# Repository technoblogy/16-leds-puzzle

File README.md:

# 16 LEDs Puzzle
A puzzle based on an ATtiny404 (or ATtiny204) in which you have to press the right buttons to light up all the LEDs.

See <http://www.technoblogy.com/show?3PO0>.

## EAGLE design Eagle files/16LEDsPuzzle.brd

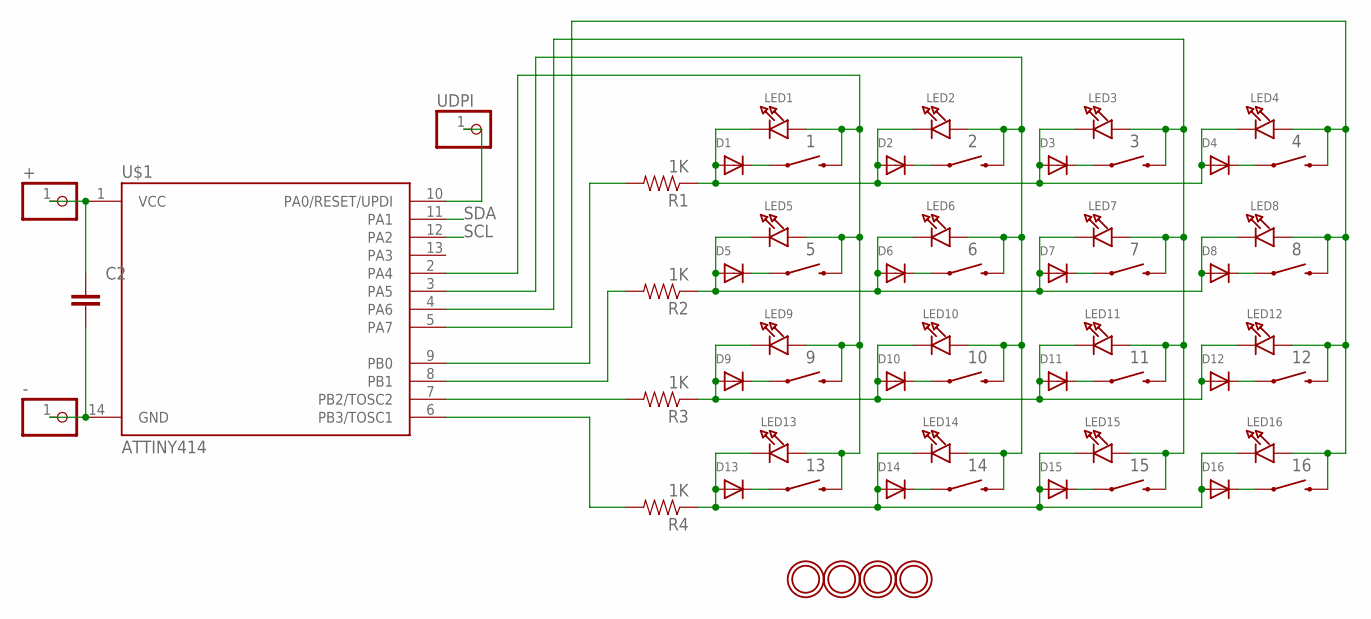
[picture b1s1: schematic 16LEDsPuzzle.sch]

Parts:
1, 2, 3, 4, 5, 6, 7, 8, 9, 10, 11, 12, 13, 14, 15, 16: SWITCH-MOMENTARY-2SMD-4; TACTILE_SWITCH_TALL
+: HEADER-1X1ROUND; 1X01_ROUND
-: HEADER-1X1ROUND; 1X01_ROUND
C2: 100n; 0805
D1, D2, D3, D4, D5, D6, D7, D8, D9, D10, D11, D12, D13, D14, D15, D16: DIODESOD-123; SOD-123
LED1, LED2, LED3, LED4, LED5, LED6, LED7, LED8, LED9, LED10, LED11, LED12, LED13, LED14, LED15, LED16: GREEN; CHIPLED_0805_NOOUTLINE
R1, R2, R3, R4: 1K; 0805
U$1: ATTINY414; SO14
U$2, U$3, U$4, U$5: MOUNTINGHOLE2.5; MOUNTINGHOLE_2.5_PLATED
UDPI: HEADER-1X1ROUND; 1X01_ROUND

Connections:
GND: -.1, C2.2, U$1.14 (GND)
unnamed: R1.2, U$1.9 (PB0)
unnamed: 1.B2 (2), 5.B2 (2), 9.B2 (2), 13.B2 (2), LED1.A, LED5.A, LED9.A, LED13.A, U$1.2 (PA4)
unnamed: 1.A2 (1), D1.C
unnamed: D1.A, D2.A, D3.A, D4.A, LED1.C, LED2.C, LED3.C, LED4.C, R1.1
unnamed: 5.A2 (1), D5.C
unnamed: 2.A2 (1), D2.C
unnamed: 2.B2 (2), 6.B2 (2), 10.B2 (2), 14.B2 (2), LED2.A, LED6.A, LED10.A, LED14.A, U$1.3 (PA5)
unnamed: D5.A, D6.A, D7.A, D8.A, LED5.C, LED6.C, LED7.C, LED8.C, R2.1
unnamed: 6.A2 (1), D6.C
unnamed: 3.A2 (1), D3.C
unnamed: R2.2, U$1.8 (PB1)
unnamed: 3.B2 (2), 7.B2 (2), 11.B2 (2), 15.B2 (2), LED3.A, LED7.A, LED11.A, LED15.A, U$1.4 (PA6)
unnamed: R3.2, U$1.7 (PB2/TOSC2)
unnamed: 4.A2 (1), D4.C
unnamed: 4.B2 (2), 8.B2 (2), 12.B2 (2), 16.B2 (2), LED4.A, LED8.A, LED12.A, LED16.A, U$1.5 (PA7)
unnamed: 7.A2 (1), D7.C
unnamed: R4.2, U$1.6 (PB3/TOSC1)
unnamed: 8.A2 (1), D8.C
unnamed: 9.A2 (1), D9.C
unnamed: D9.A, D10.A, D11.A, D12.A, LED9.C, LED10.C, LED11.C, LED12.C, R3.1
unnamed: 10.A2 (1), D10.C
unnamed: 11.A2 (1), D11.C
unnamed: U$1.10 (PA0/RESET/UPDI), UDPI.1
unnamed: 12.A2 (1), D12.C
unnamed: 13.A2 (1), D13.C
unnamed: D13.A, D14.A, D15.A, D16.A, LED13.C, LED14.C, LED15.C, LED16.C, R4.1
unnamed: 14.A2 (1), D14.C
unnamed: 15.A2 (1), D15.C
unnamed: 16.A2 (1), D16.C
SCL: U$1.12 (PA2)
SDA: U$1.11 (PA1)
VCC: +.1, C2.1, U$1.1 (VCC)

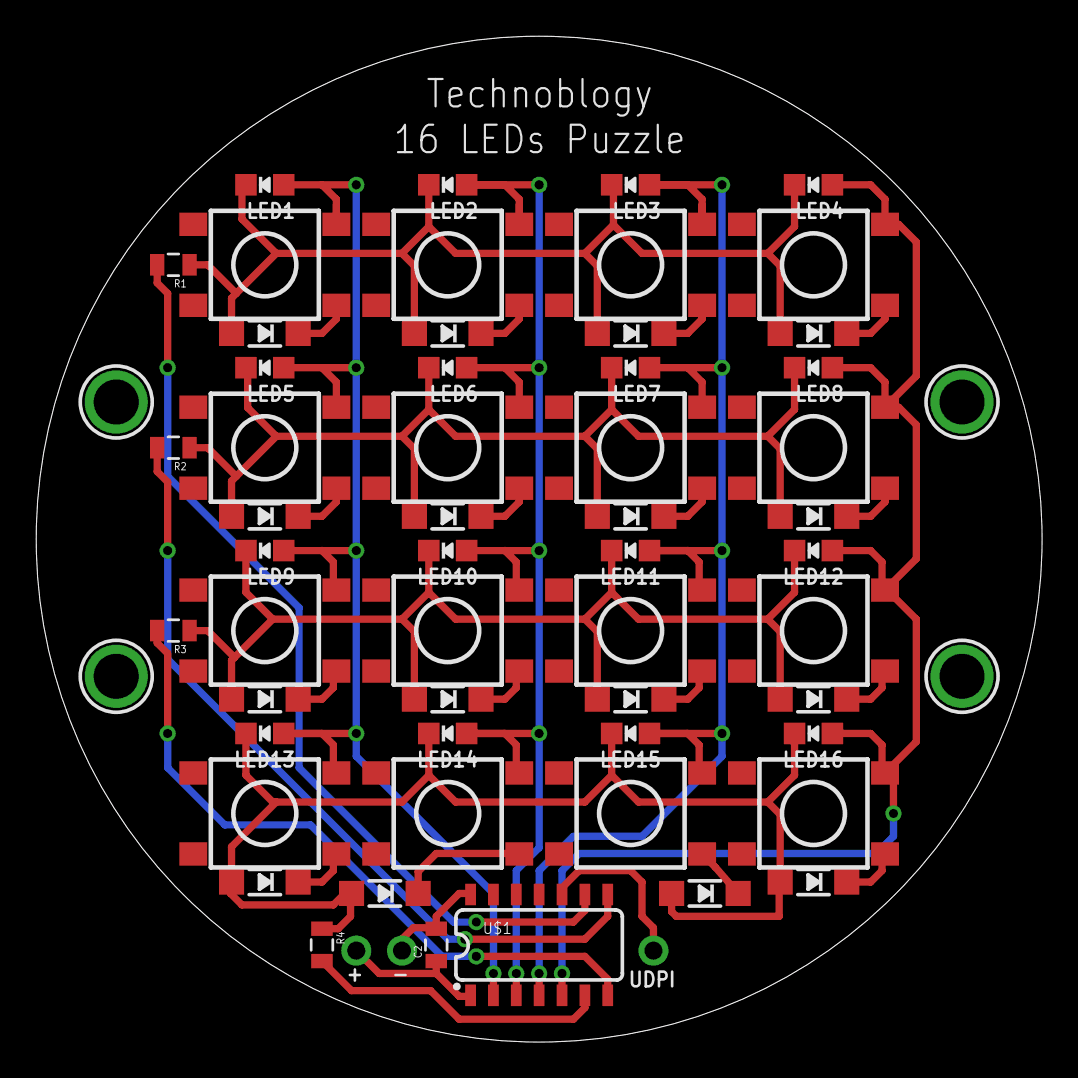
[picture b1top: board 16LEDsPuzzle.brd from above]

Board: 2 copper layers, 55.9 x 55.9 mm, 61 parts (0 on the bottom side), 31 nets.

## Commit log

2021-12-04 Version 1 - 4th December 2021

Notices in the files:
parts and their libraries:
SparkFun-Electromechanical: Licensing: Creative Commons ShareAlike 4.0 International - https://creativecommons.org/licenses/by-sa/4.0
microbuilder: This work is placed in the public domain, and may be freely used for commercial and non-commercial work with the following conditions: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
